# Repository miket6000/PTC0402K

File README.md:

# PTC0402K
A fully isolated (channel to channel and channel to input) four channel, two output programmable temperature controller and logger.

This project was built with a few target features in mind:
- Four input channels with at least 0.5C accuracy.
- SCPI interface to interface cleanly with the rest of my lab setup.
- Complete isolation of each channel (at least 230VAC) both between channels and between mains. This allows you to put a thermocouple directly on a live heatsink without risk of damaging the device or anything attached to the other thermocouples.
- A couple of relay outputs for potentially controlling heaters or coolers to allow temperature control.
- USB Type-C for both power and communications for simple setup.

A lot of inspiration came from the very nice project by Jana Marie at  

## Status
### Hardware
Rev 1 hardware has arrived. There is a fault in the current schematic where the digital isolators all drive the DO lines, even when their CS line is high. This kills the entire SPI bus. In my Rev 1 hardware I have corrected this by adding a small N-Channel MOSFET between the isolator's output enable pin and ground which is switched by the CS line. This means that normally the output is disabled on all isolators, but is enabled when the CS line is pulled low.

A bigger issue appears to be the temperature error in measureing the cold side junction. Because of the proximity of the MAX31855 to the isolated DCDC converter (which gets warm) and the distance to the thermocouple connector, there can be an error in the reported cold side junction temperature. As thermocouples are differnetial temperature devices, this directly adds to the temperature of the measurement. It looks like this is somewhere in the vicinty of 2-3 degrees C, however this depends on the ambient temperature and how long the entire device is powered which makes it difficult to calibrate out. 

Rev 2 will include the CS line fix and also add external flash to allow on board logging. I'm debating the merits of including a 32kHz crystal for the built in RTC (but then, do I also want a backup battery...) and might end up upgrading the STM32F072 to an STM32F078 for the additional ROM. For the cold junction offset issue I'm still debating options. I could simply move the MAX31855 closer to the junction and further from the DCDC converter, or I could add an additional temperature sensor to the junction itself and provide proper automatic calibration in SW. If I go that path however I end up with a highly integrated solution where I'm effectively not relying on any of the integration and I'd probably be better off with a 16-24bit DAC and discrete voltage reference and an analogue muxer, however this would take up more board space and likely end up costing more.

### Software
A basic test firmware has been written which reads the hot and cold junction temperatures, as well as the thermocouple status and allows them to be read via SCPI. It also allows control of the output relays though no temperature controller or alarms have been written.

The math for computing the corrected NIST polynomial based temperatures is all calculated using fixed point math as there is no FPU in the STM32F072. Rather than computing the polynomials directly on the uC this was done offline to create a lookup table. This is both faster than using floats and more accurate than using fixed point the whole way through as we can use true double precision during intermediate steps of the calculations and only drop to the 16.16 fixed precision format for the final lookup.

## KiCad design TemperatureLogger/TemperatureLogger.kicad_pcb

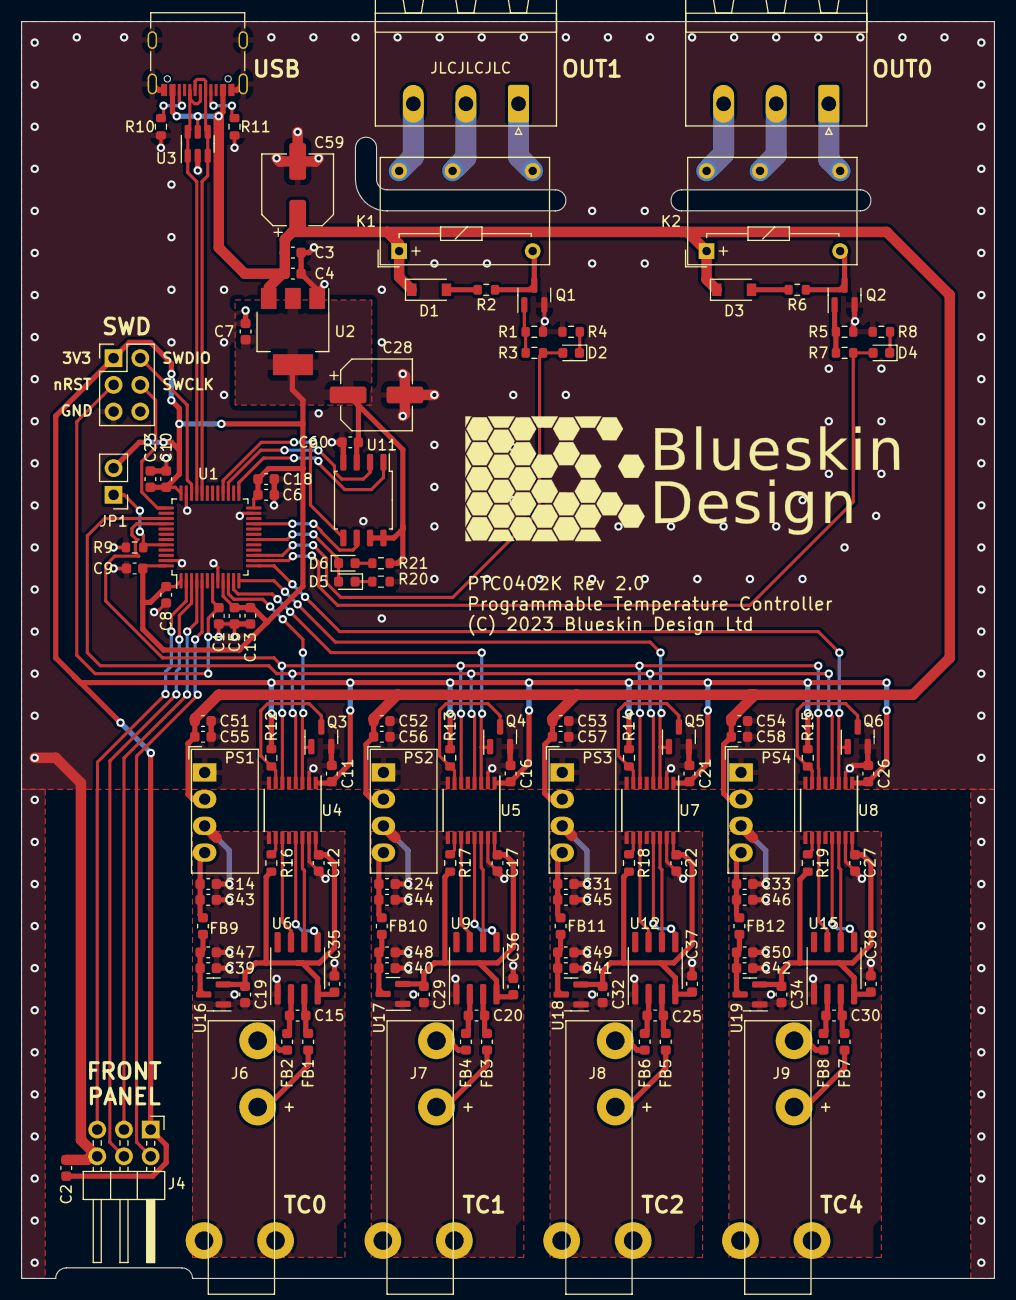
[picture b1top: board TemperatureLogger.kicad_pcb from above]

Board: 2 copper layers, 92.5 x 119.5 mm, 137 parts (0 on the bottom side), 96 nets.

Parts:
C1, C2, C4, C6, C7, C8, C9, C10, C11, C12, C14, C16, C17, C19, C21, C22, C24, C26, C27, C29, C31, C32, C33, C34, C35, C36, C37, C38, C39, C40, C41, C42, C55, C56, C57, C58, C60: 100n; C_0603_1608Metric
C3, C13: 1u; C_0603_1608Metric
C5, C15, C20, C25, C30: 10n; C_0603_1608Metric
C18, C23: 4u7; C_0603_1608Metric
C28, C59: 220u; CP_Elec_6.3x7.7
C43, C44, C45, C46, C47, C48, C49, C50, C51, C52, C53, C54: 22u; C_0603_1608Metric
D1, D3: 1N4148; D_SOD-123
D2, D4, D6: LED_GREEN; LED_0603_1608Metric
D5: LED_RED; LED_0603_1608Metric
FB1, FB2, FB3, FB4, FB5, FB6, FB7, FB8, FB9, FB10, FB11, FB12: 600R; L_0603_1608Metric
J1, J2: OUTPUT; PhoenixContact_MSTBA_2,5_3-G_1x03_P5.00mm_Horizontal
J3: USB_C_Receptacle_USB2.0; USB_C_Receptacle_Palconn_UTC16-G
J4: Conn_02x03_Odd_Even; PinHeader_2x03_P2.54mm_Horizontal
J5: Conn_02x03_Odd_Even; PinHeader_2x03_P2.54mm_Vertical
J6, J7, J8, J9: TC_BLOCK; PCC-SMP-V
JP1: Jumper_2_Bridged; PinHeader_1x02_P2.54mm_Vertical
K1, K2: G6E; Relay_SPDT_Omron_G6E
PS1, PS2, PS3, PS4: B0505S-1W; Converter_DCDC_Murata_MEE1SxxxxSC_THT
Q1, Q2: BC847C; SOT-23
Q3, Q4, Q5, Q6: Q_NMOS_GSD; SOT-23
R1, R3, R5, R7, R9, R10, R11, R12, R13, R14, R15, R16, R17, R18, R19: 5k1; R_0603_1608Metric
R2, R4, R6, R8, R20, R21: 620; R_0603_1608Metric
U1: STM32F072C8Tx; LQFP-48_7x7mm_P0.5mm
U2: AMS1117-3.3; SOT-223-3_TabPin2
U3: USBLC6-2SC6; SOT-23-6
U4, U5, U7, U8: ISO7741DBQR; SSOP-16_3.9x4.9mm_P0.635mm
U6, U9, U12, U15: MAX31855KASA; SOIC-8_3.9x4.9mm_P1.27mm
U11: W25Q128JV; SOIC-8_5.275x5.275mm_P1.27mm
U16, U17, U18, U19: MCP1700x-330xxTT; SOT-23

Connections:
+3.3V: C2.1, C5.1, C6.1, C7.1, C8.1, C9.1, C10.1, C11.1, C13.1, C16.1, C18.1, C21.1, C23.1, C26.1, C28.1, C60.1, J4.1, J5.1, JP1.2 (B), R12.2, R13.2, R14.2, R15.2, R21.2, U1.1 (VBAT), U1.9 (VDDA), U1.24 (VDD), U1.36 (VDDIO2), U1.48 (VDD), U2.2 (VO), U4.1 (VDD1), U5.1 (VDD1), U7.1 (VDD1), U8.1 (VDD1), U11.3 (~WP), U11.7 (~HOLD), U11.8 (VCC)
+5V: C3.1, C4.1, C51.1, C52.1, C53.1, C54.1, C55.1, C56.1, C57.1, C58.1, C59.1, D1.1 (K), D3.1 (K), J3.A4 (VBUS), J3.A9 (VBUS), J3.B4 (VBUS), J3.B9 (VBUS), K1.1, K2.1, PS1.2 (+Vin), PS2.2 (+Vin), PS3.2 (+Vin), PS4.2 (+Vin), U2.3 (VI), U3.5 (VBUS)
/CS0: Q3.1 (G), U1.10 (PA0), U4.3 (VIA)
/CS1: Q4.1 (G), U1.11 (PA1), U5.3 (VIA)
/CS2: Q5.1 (G), U1.12 (PA2), U7.3 (VIA)
/CS3: Q6.1 (G), U1.13 (PA3), U8.3 (VIA)
/D+: J3.A6 (D+), J3.B6 (D+), U1.33 (PA12), U3.1 (I/O1), U3.6 (I/O1)
/D-: J3.A7 (D-), J3.B7 (D-), U1.32 (PA11), U3.3 (I/O2), U3.4 (I/O2)
/LED0: J4.2, U1.5 (PF0)
/LED1: J4.3, U1.4 (PC15)
/LED2: J4.4, U1.3 (PC14)
/LED3: J4.5, U1.2 (PC13)
/LED_DEBUG: D5.2 (A), D6.1 (K), U1.18 (PB0)
/MEM_CS: U1.25 (PB12), U11.1 (~CS)
/MEM_MISO: U1.27 (PB14), U11.2 (DO(IO1))
/MEM_MOSI: U1.28 (PB15), U11.5 (DI(IO0))
/MEM_SCK: U1.21 (PB10), U11.6 (SCK)
/MISO: U1.40 (PB4), U4.6 (VOD), U5.6 (VOD), U7.6 (VOD), U8.6 (VOD)
/OUT0: D4.2 (A), R7.2, U1.14 (PA4)
/OUT1: D2.2 (A), R3.2, U1.15 (PA5)
/SCK: U1.39 (PB3), U4.4 (VIB), U5.4 (VIB), U7.4 (VIB), U8.4 (VIB)
/SWCLK: J5.4, U1.37 (PA14)
/SWDIO: J5.2, U1.34 (PA13)
/TC_Channel0/3V3ISO: C12.1, C19.1, C35.1, R16.2, U4.16 (VDD2), U6.4 (VCC), U16.2 (VO)
/TC_Channel0/5VISO: C39.1, C47.1, FB9.2, U16.3 (VI)
/TC_Channel0/CSISO: U4.14 (VOA), U6.6 (~CS)
/TC_Channel0/GNDISO: C12.2, C14.2, C19.2, C35.2, C39.2, C43.2, C47.2, J6.3, PS1.3 (-Vout), U4.9 (GND2), U4.15 (GND2), U6.1 (GND), U16.1 (GND)
/TC_Channel0/MISOISO: U4.11 (VID), U6.7 (SO)
/TC_Channel0/SCKISO: U4.13 (VOB), U6.5 (SCK)
/TC_Channel0/TC+: FB1.1, J6.1
/TC_Channel0/TC-: FB2.1, J6.2
/TC_Channel1/3V3ISO: C17.1, C29.1, C36.1, R17.2, U5.16 (VDD2), U9.4 (VCC), U17.2 (VO)
/TC_Channel1/5VISO: C40.1, C48.1, FB10.2, U17.3 (VI)
/TC_Channel1/CSISO: U5.14 (VOA), U9.6 (~CS)
/TC_Channel1/GNDISO: C17.2, C24.2, C29.2, C36.2, C40.2, C44.2, C48.2, J7.3, PS2.3 (-Vout), U5.9 (GND2), U5.15 (GND2), U9.1 (GND), U17.1 (GND)
/TC_Channel1/MISOISO: U5.11 (VID), U9.7 (SO)
/TC_Channel1/SCKISO: U5.13 (VOB), U9.5 (SCK)
/TC_Channel1/TC+: FB3.1, J7.1
/TC_Channel1/TC-: FB4.1, J7.2
/TC_Channel2/3V3ISO: C22.1, C32.1, C37.1, R18.2, U7.16 (VDD2), U12.4 (VCC), U18.2 (VO)
/TC_Channel2/5VISO: C41.1, C49.1, FB11.2, U18.3 (VI)
/TC_Channel2/CSISO: U7.14 (VOA), U12.6 (~CS)
/TC_Channel2/GNDISO: C22.2, C31.2, C32.2, C37.2, C41.2, C45.2, C49.2, J8.3, PS3.3 (-Vout), U7.9 (GND2), U7.15 (GND2), U12.1 (GND), U18.1 (GND)
/TC_Channel2/MISOISO: U7.11 (VID), U12.7 (SO)
/TC_Channel2/SCKISO: U7.13 (VOB), U12.5 (SCK)
/TC_Channel2/TC+: FB5.1, J8.1
/TC_Channel2/TC-: FB6.1, J8.2
/TC_Channel3/3V3ISO: C27.1, C34.1, C38.1, R19.2, U8.16 (VDD2), U15.4 (VCC), U19.2 (VO)
/TC_Channel3/5VISO: C42.1, C50.1, FB12.2, U19.3 (VI)
/TC_Channel3/CSISO: U8.14 (VOA), U15.6 (~CS)
/TC_Channel3/GNDISO: C27.2, C33.2, C34.2, C38.2, C42.2, C46.2, C50.2, J9.3, PS4.3 (-Vout), U8.9 (GND2), U8.15 (GND2), U15.1 (GND), U19.1 (GND)
/TC_Channel3/MISOISO: U8.11 (VID), U15.7 (SO)
/TC_Channel3/SCKISO: U8.13 (VOB), U15.5 (SCK)
/TC_Channel3/TC+: FB7.1, J9.1
/TC_Channel3/TC-: FB8.1, J9.2
/nRST: C1.1, J5.3, U1.7 (NRST)
GND: C1.2, C2.2, C3.2, C4.2, C5.2, C6.2, C7.2, C8.2, C9.2, C10.2, C11.2, C13.2, C16.2, C18.2, C21.2, C23.2, C26.2, C28.2, C51.2, C52.2, C53.2, C54.2, C55.2, C56.2, C57.2, C58.2, C59.2, C60.2, J3.A1 (GND), J3.A12 (GND), J3.B1 (GND), J3.B12 (GND), J3.S1 (SHIELD), J4.6, J5.5, PS1.1 (-Vin), PS2.1 (-Vin), PS3.1 (-Vin), PS4.1 (-Vin), Q1.2 (E), Q2.2 (E), Q3.2 (S), Q4.2 (S), Q5.2 (S), Q6.2 (S), R1.1, R4.1, R5.1, R8.1, R9.2, R10.2, R11.2, R20.1, U1.8 (VSSA), U1.23 (VSS), U1.35 (VSS), U1.47 (VSS), U2.1 (GND), U3.2 (GND), U4.2 (GND1), U4.8 (GND1), U5.2 (GND1), U5.8 (GND1), U7.2 (GND1), U7.8 (GND1), U8.2 (GND1), U8.8 (GND1), U11.4 (GND)
unnamed: D1.2 (A), R2.2
unnamed: D2.1 (K), R4.2
unnamed: D3.2 (A), R6.2
unnamed: D4.1 (K), R8.2
unnamed: D5.1 (K), R20.2
unnamed: D6.2 (A), R21.1
unnamed: J1.1, K1.7
unnamed: J1.2, K1.10
unnamed: J1.3, K1.12
unnamed: J2.1, K2.7
unnamed: J2.2, K2.10
unnamed: J2.3, K2.12
unnamed: J3.A5 (CC1), R11.1
unnamed: J3.B5 (CC2), R10.1
unnamed: JP1.1 (A), R9.1, U1.44 (BOOT0)
unnamed: C14.1, C43.1, FB9.1, PS1.4 (+Vout)
unnamed: C24.1, C44.1, FB10.1, PS2.4 (+Vout)
unnamed: C31.1, C45.1, FB11.1, PS3.4 (+Vout)
unnamed: C33.1, C46.1, FB12.1, PS4.4 (+Vout)
unnamed: Q1.1 (B), R1.2, R3.1
unnamed: K1.6, Q1.3 (C), R2.1
unnamed: Q2.1 (B), R5.2, R7.1
unnamed: K2.6, Q2.3 (C), R6.1
unnamed: Q3.3 (D), R12.1, U4.7 (CTRL1)
unnamed: Q4.3 (D), R13.1, U5.7 (CTRL1)
unnamed: Q5.3 (D), R14.1, U7.7 (CTRL1)
unnamed: Q6.3 (D), R15.1, U8.7 (CTRL1)
unnamed: R16.1, U4.10 (CTRL2)
unnamed: R17.1, U5.10 (CTRL2)
unnamed: C15.1, FB1.2, U6.3 (T+)
unnamed: C15.2, FB2.2, U6.2 (T-)
unnamed: R18.1, U7.10 (CTRL2)
unnamed: R19.1, U8.10 (CTRL2)
unnamed: C20.1, FB3.2, U9.3 (T+)
unnamed: C20.2, FB4.2, U9.2 (T-)
unnamed: C25.1, FB5.2, U12.3 (T+)
unnamed: C25.2, FB6.2, U12.2 (T-)
unnamed: C30.1, FB7.2, U15.3 (T+)
unnamed: C30.2, FB8.2, U15.2 (T-)

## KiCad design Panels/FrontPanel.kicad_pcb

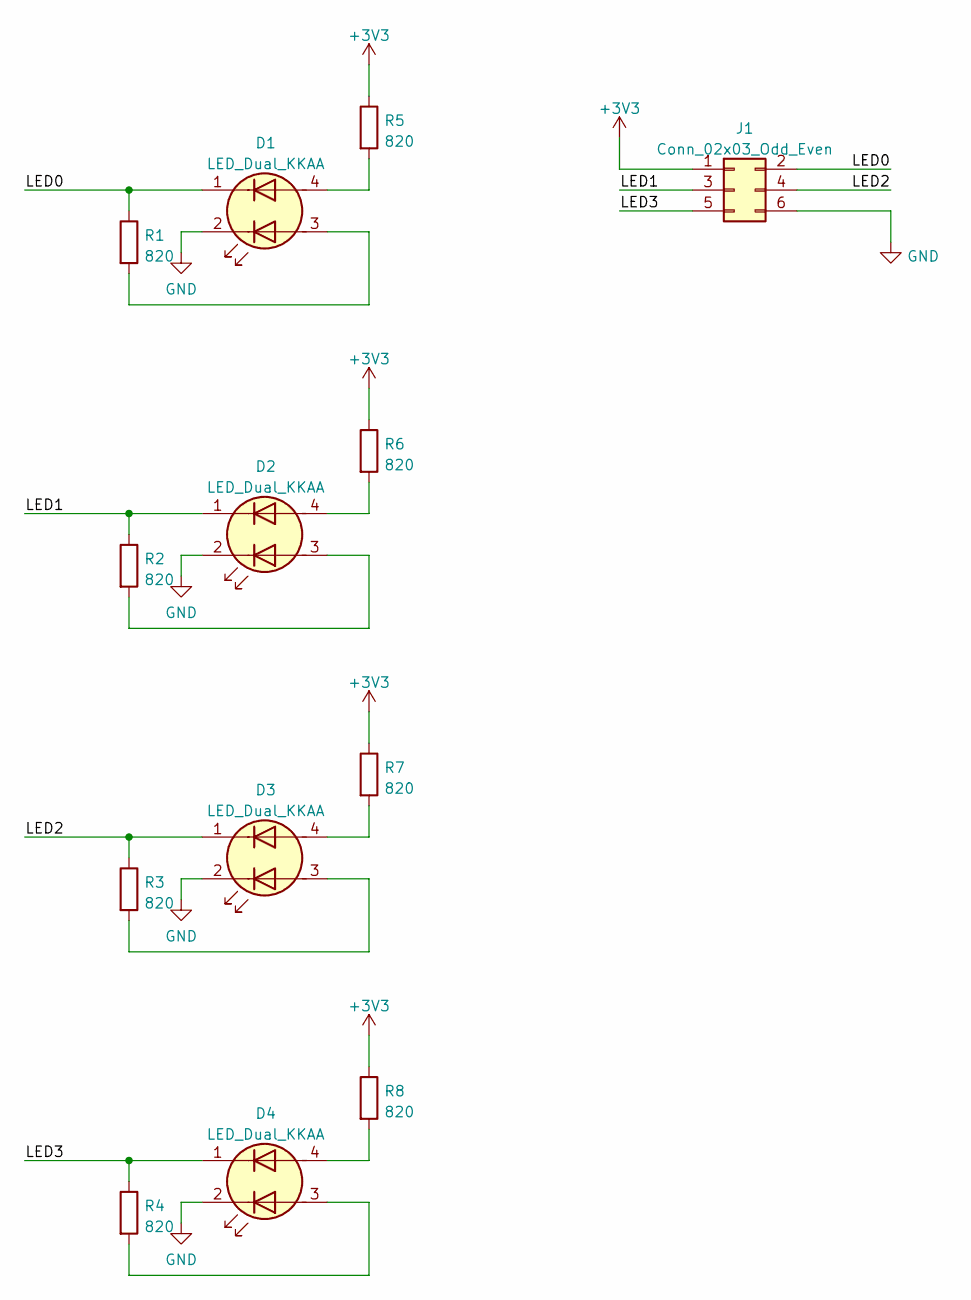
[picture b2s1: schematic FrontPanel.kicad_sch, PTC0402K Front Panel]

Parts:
D1, D2, D3, D4: LED_Dual_KKAA; Wurth_Bicolor_Reverse_Mount_LED
J1: Conn_02x03_Odd_Even; PinSocket_2x03_P2.54mm_Vertical_SMD
R1, R2, R3, R4, R5, R6, R7, R8: 820; R_0603_1608Metric_Pad0.98x0.95mm_HandSolder

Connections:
+3V3: J1.1, R5.1, R6.1, R7.1, R8.1
/LED0: D1.1 (K2), J1.2, R1.1
/LED1: D2.1 (K2), J1.3, R2.1
/LED2: D3.1 (K2), J1.4, R3.1
/LED3: D4.1 (K2), J1.5, R4.1
GND: D1.2 (K1), D2.2 (K1), D3.2 (K1), D4.2 (K1), J1.6
unnamed: D1.3 (A1), R1.2
unnamed: D1.4 (A2), R5.2
unnamed: D2.3 (A1), R2.2
unnamed: D2.4 (A2), R6.2
unnamed: D3.3 (A1), R3.2
unnamed: D3.4 (A2), R7.2
unnamed: D4.3 (A1), R4.2
unnamed: D4.4 (A2), R8.2

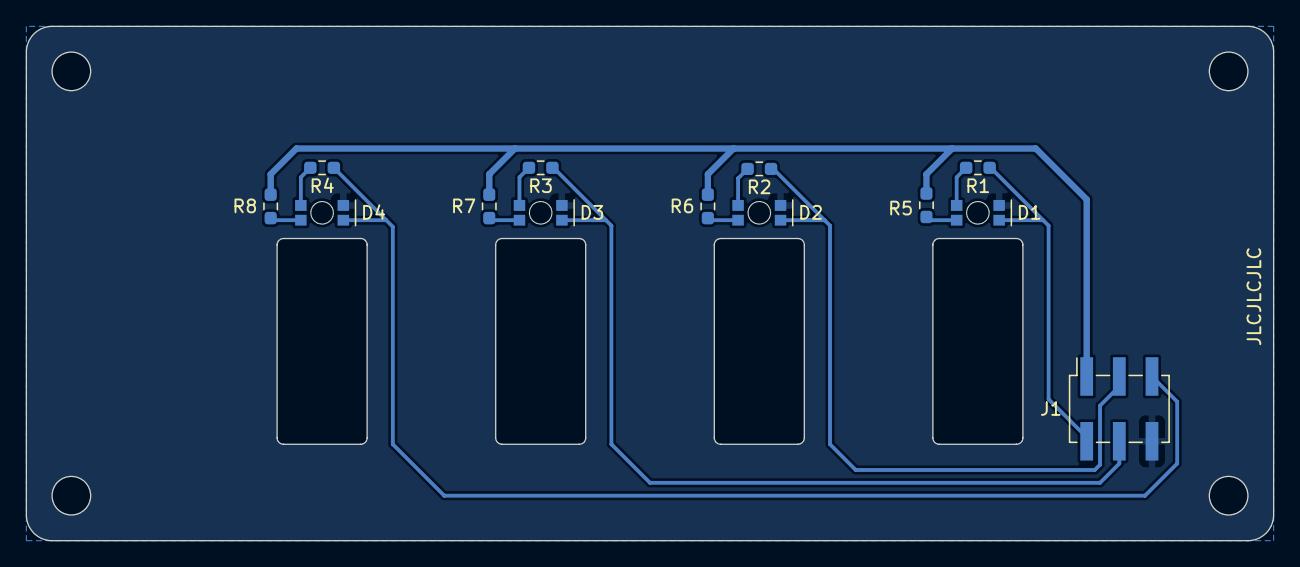
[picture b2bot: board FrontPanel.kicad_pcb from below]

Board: 2 copper layers, 97.0 x 40.0 mm, 13 parts (13 on the bottom side), 14 nets.

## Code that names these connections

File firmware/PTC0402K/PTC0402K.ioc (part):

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Mcu.Name=STM32F072C(8-B)Tx
Mcu.Package=LQFP48
Mcu.UserName=STM32F072C8Tx
PA0.GPIOParameters=PinState,GPIO_Label
PA0.GPIO_Label=CS0
PA0.PinState=GPIO_PIN_SET
PA0.Signal=GPIO_Output
PA1.GPIOParameters=PinState,GPIO_Label
PA1.GPIO_Label=CS1
PA1.PinState=GPIO_PIN_SET
PA1.Signal=GPIO_Output
PA11.Mode=Device
PA11.Signal=USB_DM
PA12.Mode=Device
PA12.Signal=USB_DP
PA13.Mode=Serial_Wire
PA13.Signal=SYS_SWDIO
PA14.Mode=Serial_Wire
PA14.Signal=SYS_SWCLK
PA2.GPIOParameters=PinState,GPIO_Label
PA2.GPIO_Label=CS2
PA2.PinState=GPIO_PIN_SET
PA2.Signal=GPIO_Output
PA3.GPIOParameters=PinState,GPIO_Label
PA3.GPIO_Label=CS3
PA3.PinState=GPIO_PIN_SET
PA3.Signal=GPIO_Output
PA4.GPIOParameters=GPIO_Label
PA4.GPIO_Label=OUT0
PA4.Signal=GPIO_Output
PA5.GPIOParameters=GPIO_Label
PA5.GPIO_Label=OUT1
PA5.Signal=GPIO_Output
PB3.Mode=RX_Only_Simplex_Unidirect_Master
PB3.Signal=SPI1_SCK
PB4.Mode=RX_Only_Simplex_Unidirect_Master
PB4.Signal=SPI1_MISO
PC13.GPIOParameters=GPIO_Label
PC13.GPIO_Label=LED3
PC13.Signal=GPIO_Input
PC14-OSC32_IN.GPIOParameters=GPIO_Label
PC14-OSC32_IN.GPIO_Label=LED2
PC14-OSC32_IN.Signal=GPIO_Input
PC15-OSC32_OUT.GPIOParameters=GPIO_Label
PC15-OSC32_OUT.GPIO_Label=LED1
PC15-OSC32_OUT.Signal=GPIO_Input
PF0-OSC_IN.GPIOParameters=GPIO_Label
PF0-OSC_IN.GPIO_Label=LED0
PF0-OSC_IN.Signal=GPIO_Input
RCC.SYSCLKFreq_VALUE=48000000
RCC.SYSCLKSource=RCC_SYSCLKSOURCE_HSI48
board=custom

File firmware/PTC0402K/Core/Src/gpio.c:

/* USER CODE BEGIN Header */
/**
  ******************************************************************************
  * @file    gpio.c
  * @brief   This file provides code for the configuration
  *          of all used GPIO pins.
  ******************************************************************************
  * @attention
  *
  * Copyright (c) 2023 STMicroelectronics.
  * All rights reserved.
  *
  * This software is licensed under terms that can be found in the LICENSE file
  * in the root directory of this software component.
  * If no LICENSE file comes with this software, it is provided AS-IS.
  *
  ******************************************************************************
  */
/* USER CODE END Header */

/* Includes ------------------------------------------------------------------*/
#include "gpio.h"

/* USER CODE BEGIN 0 */

/* USER CODE END 0 */

/*----------------------------------------------------------------------------*/
/* Configure GPIO                                                             */
/*----------------------------------------------------------------------------*/
/* USER CODE BEGIN 1 */

/* USER CODE END 1 */

/** Configure pins as
        * Analog
        * Input
        * Output
        * EVENT_OUT
        * EXTI
        * Free pins are configured automatically as Analog (this feature is enabled through
        * the Code Generation settings)
*/
void MX_GPIO_Init(void)
{

  GPIO_InitTypeDef GPIO_InitStruct = {0};

  /* GPIO Ports Clock Enable */
  __HAL_RCC_GPIOC_CLK_ENABLE();
  __HAL_RCC_GPIOF_CLK_ENABLE();
  __HAL_RCC_GPIOA_CLK_ENABLE();
  __HAL_RCC_GPIOB_CLK_ENABLE();

  /*Configure GPIO pin Output Level */
  HAL_GPIO_WritePin(GPIOA, CS0_Pin|CS1_Pin|CS2_Pin|CS3_Pin, GPIO_PIN_SET);

  /*Configure GPIO pin Output Level */
  HAL_GPIO_WritePin(GPIOA, OUT0_Pin|OUT1_Pin, GPIO_PIN_RESET);

  /*Configure GPIO pins : PCPin PCPin PCPin */
  GPIO_InitStruct.Pin = LED3_Pin|LED2_Pin|LED1_Pin;
  GPIO_InitStruct.Mode = GPIO_MODE_INPUT;
  GPIO_InitStruct.Pull = GPIO_NOPULL;
  HAL_GPIO_Init(GPIOC, &GPIO_InitStruct);

  /*Configure GPIO pin : PtPin */
  GPIO_InitStruct.Pin = LED0_Pin;
  GPIO_InitStruct.Mode = GPIO_MODE_INPUT;
  GPIO_InitStruct.Pull = GPIO_NOPULL;
  HAL_GPIO_Init(LED0_GPIO_Port, &GPIO_InitStruct);

  /*Configure GPIO pin : PF1 */
  GPIO_InitStruct.Pin = GPIO_PIN_1;
  GPIO_InitStruct.Mode = GPIO_MODE_ANALOG;
  GPIO_InitStruct.Pull = GPIO_NOPULL;
  HAL_GPIO_Init(GPIOF, &GPIO_InitStruct);

  /*Configure GPIO pins : PAPin PAPin PAPin PAPin
                           PAPin PAPin */
  GPIO_InitStruct.Pin = CS0_Pin|CS1_Pin|CS2_Pin|CS3_Pin
                          |OUT0_Pin|OUT1_Pin;
  GPIO_InitStruct.Mode = GPIO_MODE_OUTPUT_PP;
  GPIO_InitStruct.Pull = GPIO_NOPULL;
  GPIO_InitStruct.Speed = GPIO_SPEED_FREQ_LOW;
  HAL_GPIO_Init(GPIOA, &GPIO_InitStruct);

  /*Configure GPIO pins : PA6 PA7 PA8 PA9
                           PA10 PA15 */
  GPIO_InitStruct.Pin = GPIO_PIN_6|GPIO_PIN_7|GPIO_PIN_8|GPIO_PIN_9
                          |GPIO_PIN_10|GPIO_PIN_15;
  GPIO_InitStruct.Mode = GPIO_MODE_ANALOG;
  GPIO_InitStruct.Pull = GPIO_NOPULL;
  HAL_GPIO_Init(GPIOA, &GPIO_InitStruct);

  /*Configure GPIO pins : PB0 PB1 PB2 PB10
                           PB11 PB12 PB13 PB14
                           PB15 PB5 PB6 PB7
                           PB8 PB9 */
  GPIO_InitStruct.Pin = GPIO_PIN_0|GPIO_PIN_1|GPIO_PIN_2|GPIO_PIN_10
                          |GPIO_PIN_11|GPIO_PIN_12|GPIO_PIN_13|GPIO_PIN_14
                          |GPIO_PIN_15|GPIO_PIN_5|GPIO_PIN_6|GPIO_PIN_7
                          |GPIO_PIN_8|GPIO_PIN_9;
  GPIO_InitStruct.Mode = GPIO_MODE_ANALOG;
  GPIO_InitStruct.Pull = GPIO_NOPULL;
  HAL_GPIO_Init(GPIOB, &GPIO_InitStruct);

}

/* USER CODE BEGIN 2 */

/* USER CODE END 2 */

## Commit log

2023-09-14 Initial commit of Rev 1
2023-09-14 Create LICENSE.md
    CERN-OHL-W
2023-09-15 updated title blocks to reflect correct license
2023-09-15 updated pdf schematic with corrected title blocks
2023-09-15 corrected initial description of PTC0402K function
2023-10-09 Initial firmware commit.
2023-10-09 Update README.md
    Updated project status after receiving boards.
2023-10-10 Updated MAX31855 files to use fixed point math. This removed the dirty hack that I was using to report floats which didn't work. I also wrote my own simplfied fixed point pow implementation so that I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
2023-10-10 updated status of SW to represet fixed point math
2023-10-12 corrected bug in NIST compensation code
2023-10-24 updated NIST compensation to use lookup tables and fixed point math for better accuracy and performance.
2023-10-24 updated README status
2023-10-25 Added buildtable.c, cleaned up file locations and updated Makefile to automatically build NIST.h
2023-10-28 fixed bug in buildtable.c, messed around with Makefile and a few other minor cleanups.
2023-10-28 added simple bangbang temperature controller and updated test.py to test it
2023-10-29 fixed error resulting from unexpected behaviour from SCPI_ParamCharacters(). Cleaned up bang-bang controller code and added option to invert output behaviour.
2023-10-30 added external flash and corrected issue with output disable for digital isolators
2023-11-01 cleaned up Makefile to fix dependancy generation and removed auto generated NIST.h file from project as it gets built during compilation

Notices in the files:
Panels/FrontPanel.kicad_pcb:
License: CERN-OHL-W
TemperatureLogger/TemperatureLogger.kicad_pcb:
(C) 2023 Blueskin Design Ltd
